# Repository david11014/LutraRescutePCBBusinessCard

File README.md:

# LutraRescutePCBBusinessCard

# Intro

瀕臨絕種團露恰露恰的 PCB 名片，靈感來自以下直播內容
[【魔女之家#2】見習小魔女水獺的新家大冒險🍻【露恰露恰．Vtuber】](https://youtu.be/RvgKsK7jW5E?t=4198)

感謝[春魚工作室](https://t.co/JhnwOmfZGn)與[里歐](https://twitter.com/leo_chen0912/status/1580262135908945920)授權使用圖片

This is a PCB business card of LutraLutra, the idea is inspired by the blow live video [【魔女之家#2】見習小魔女水獺的新家大冒險🍻【露恰露恰．Vtuber】](https://youtu.be/RvgKsK7jW5E?t=4198).

Thanks to [春魚工作室](https://t.co/JhnwOmfZGn) and [里歐](https://twitter.com/leo_chen0912/status/1580262135908945920) for the permission to use image.

# BOM
|Ref                     |Qnty |Value        |Footprint                                                  |Description                                     |Vendor                             |
|------------------------|-----|-------------|-----------------------------------------------------------|------------------------------------------------|-----------------------------------|
|BT1,                    |1    |Battery_Cell |Battery:BatteryHolder_Keystone_1060_1x2032                 |Single-cell battery                             |https://ok.100y.com.tw/Goods/52684 |
|C1,                     |1    |0.1uF        |Capacitor_SMD:C_0805_2012Metric_Pad1.18x1.45mm_HandSolder  |Unpolarized capacitor                           |https://ok.100y.com.tw/Goods/99587 |
|C2, C3, C4, C5,         |4    |10uF         |Capacitor_SMD:C_0805_2012Metric_Pad1.18x1.45mm_HandSolder  |Unpolarized capacitor                           |https://ok.100y.com.tw/Goods/42857 |
|C6,                     |1    |0.001uF      |Capacitor_SMD:C_0805_2012Metric_Pad1.18x1.45mm_HandSolder  |Unpolarized capacitor                           |https://ok.100y.com.tw/Goods/124188|
|D1, D2, D3, D4, D5, D6  |6    |LED          |Img:LED_0805_2012Metric_Pad1.15x1.40mm_HandSolder          |Light emitting diode                            |https://ok.100y.com.tw/Goods/99164 |
|R1, R2,                 |2    |100K         |Resistor_SMD:R_0805_2012Metric_Pad1.20x1.40mm_HandSolder   |Resistor                                        |https://ok.100y.com.tw/Goods/123451|
|R3, R4, R5, R6, R7, R8, |6    |2K           |Resistor_SMD:R_0805_2012Metric_Pad1.20x1.40mm_HandSolder   |Resistor                                        |https://ok.100y.com.tw/Goods/123312|
|SW1,                    |1    |SW_DPDT_x2   |Img:Switch_MSK-01A                                         |Switch, dual pole double throw, separate symbols|https://ok.100y.com.tw/Goods/139685|
|SW2,                    |1    |SW_Push      |Button_Switch_SMD:SW_SPST_TL3342                           |Push button switch, generic, two pins           |https://ok.100y.com.tw/Goods/98045 |
|U1,                     |1    |LMC555CM/NOPB|Package_SO:SOIC-8_3.9x4.9mm_P1.27mm                        |CMOS Timer, 555 compatible, SOIC-8              |https://ok.100y.com.tw/Goods/56713 |

# License

<br />本著作係採用<a rel="license" href="http://creativecommons.org/licenses/by-nc-sa/4.0/">創用 CC 姓名標示-非商業性-相同方式分享 4.0 國際 授權條款</a>授權.

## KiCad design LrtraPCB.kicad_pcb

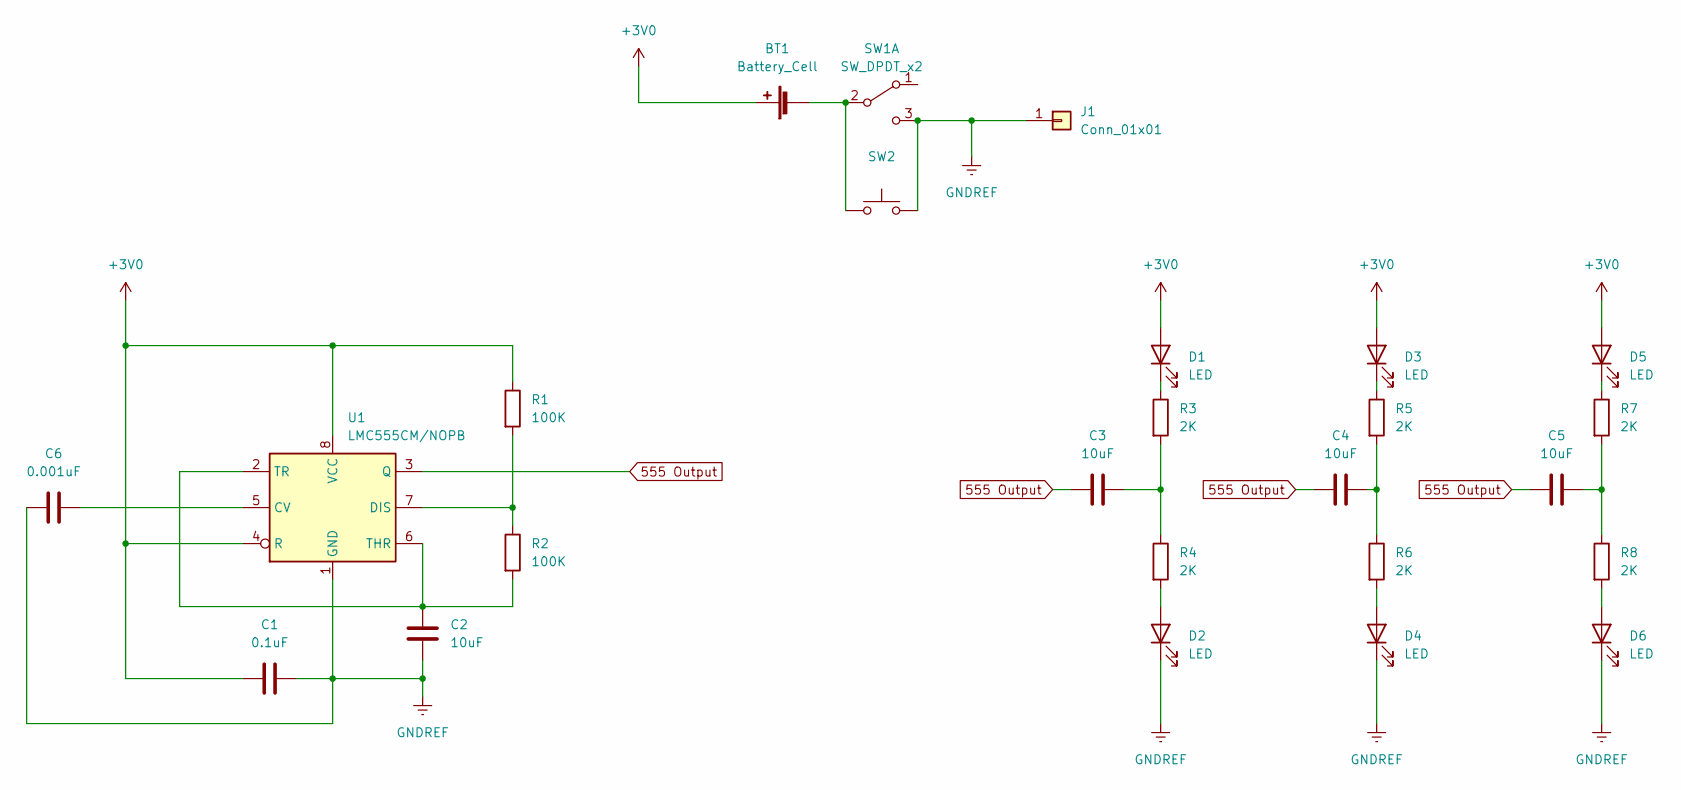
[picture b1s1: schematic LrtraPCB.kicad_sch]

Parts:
BT1: Battery_Cell; BatteryHolder_Keystone_1060_1x2032
C1: 0.1uF; C_0805_2012Metric_Pad1.18x1.45mm_HandSolder
C2, C3, C4, C5: 10uF; C_0805_2012Metric_Pad1.18x1.45mm_HandSolder
C6: 0.001uF; C_0805_2012Metric_Pad1.18x1.45mm_HandSolder
D1, D4, D5: LED; LED_0805_2012Metric_Pad1.15x1.40mm_HandSolder_Flower_small
D2, D3, D6: LED; LED_0805_2012Metric_Pad1.15x1.40mm_HandSolder_Flower
J1: Conn_01x01; Lutra_QRCode
R1, R2: 100K; R_0805_2012Metric_Pad1.20x1.40mm_HandSolder
R3, R4, R5, R6, R7, R8: 2K; R_0805_2012Metric_Pad1.20x1.40mm_HandSolder
SW1: SW_DPDT_x2; Switch_MSK-01A
SW2: SW_Push; SW_SPST_TL3342
U1: LMC555CM/NOPB; SOIC-8_3.9x4.9mm_P1.27mm

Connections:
555 Output: C3.1, C4.1, C5.1, U1.3 (Q)
+3V0: BT1.1 (+), C1.2, D1.2 (A), D3.2 (A), D5.2 (A), R1.1, U1.4 (R), U1.8 (VCC)
GNDREF: C1.1, C2.2, C6.2, D2.1 (K), D4.1 (K), D6.1 (K), J1.1, SW1.3 (C), SW1.4 (A), SW2.2, U1.1 (GND); also elsewhere on the board
unnamed 3: BT1.2 (-), SW1.2 (B), SW2.1; also elsewhere on the board
unnamed: C2.1, R2.2, U1.2 (TR), U1.6 (THR)
unnamed: C3.2, R3.2, R4.1
unnamed: C4.2, R5.2, R6.1
unnamed: C5.2, R7.2, R8.1
unnamed: C6.1, U1.5 (CV)
unnamed: D1.1 (K), R3.1
unnamed: D2.2 (A), R4.2
unnamed: D3.1 (K), R5.1
unnamed: D4.2 (A), R6.2
unnamed: D5.1 (K), R7.1
unnamed: D6.2 (A), R8.2
unnamed: R1.2, R2.1, U1.7 (DIS)

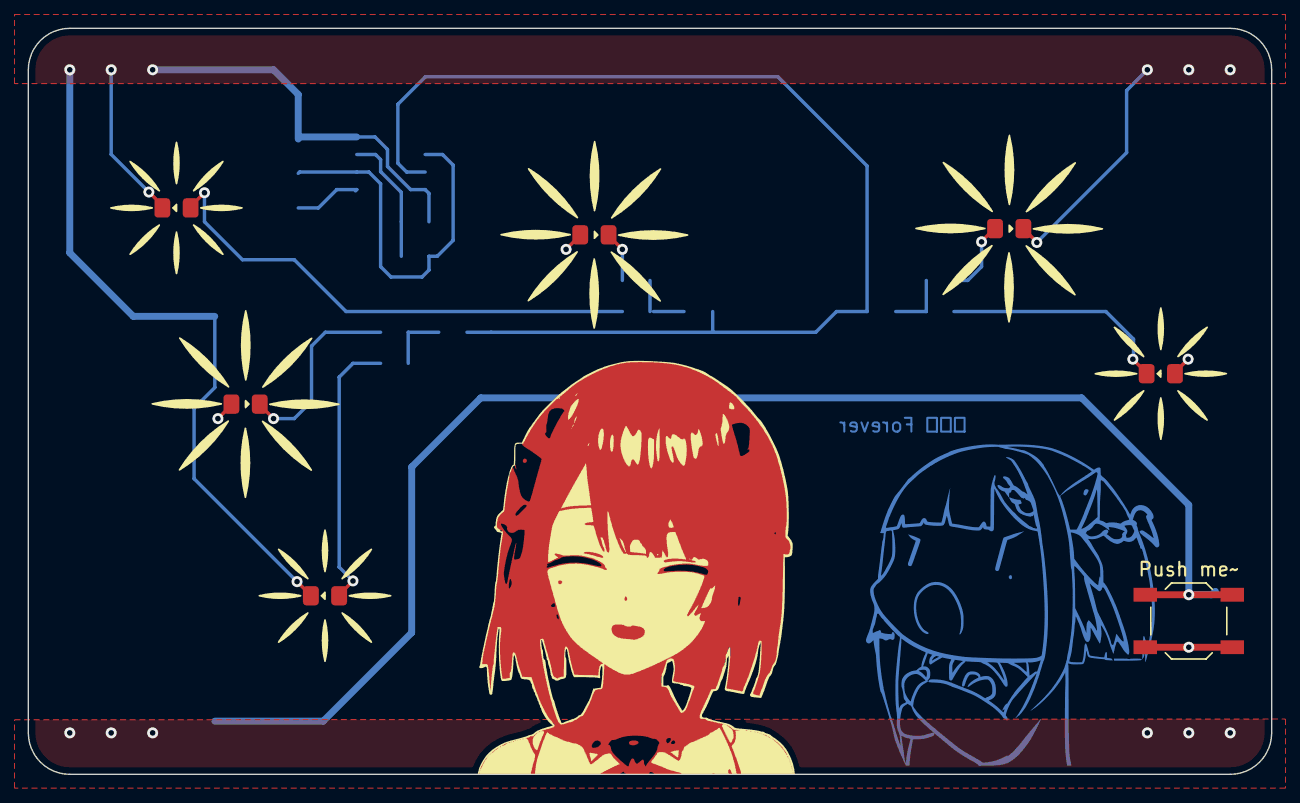
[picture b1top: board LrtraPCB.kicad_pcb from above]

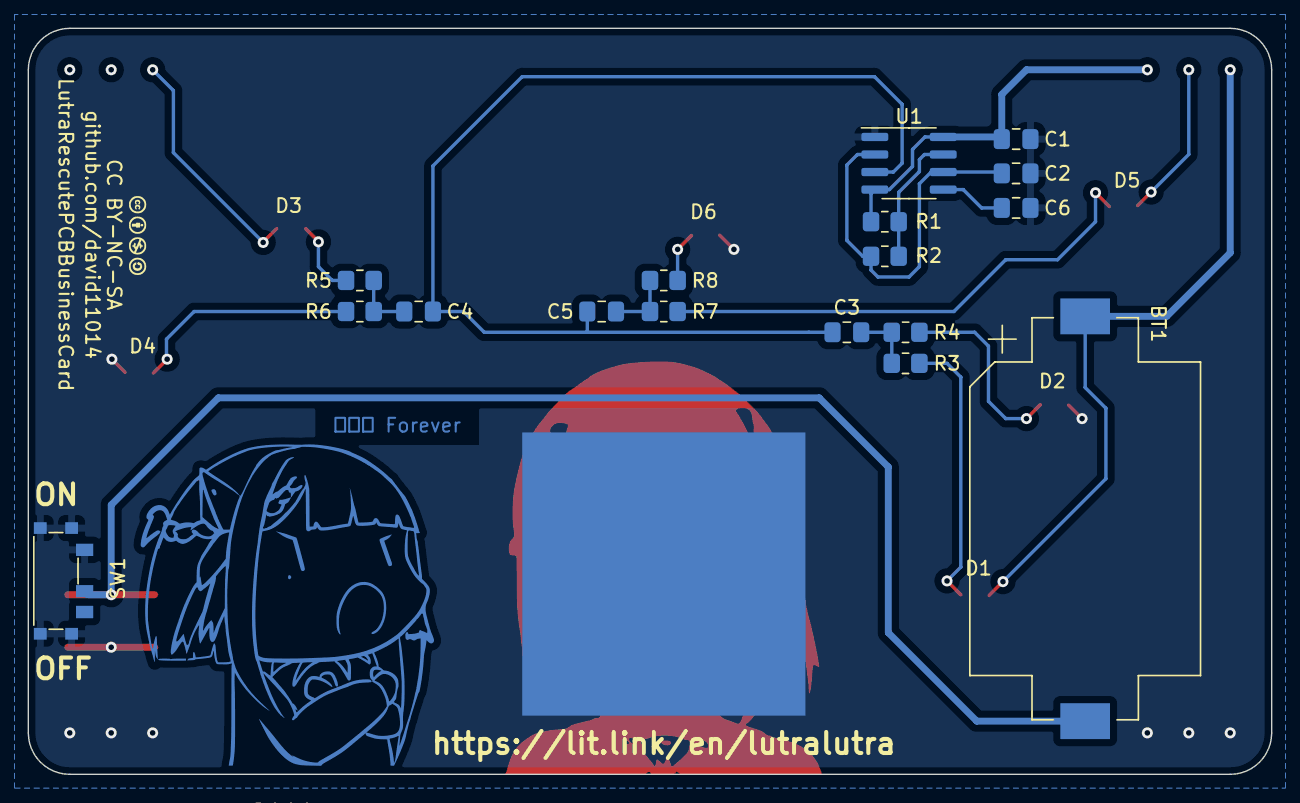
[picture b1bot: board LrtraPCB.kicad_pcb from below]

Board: 2 copper layers, 90.0 x 54.0 mm, 26 parts (19 on the bottom side), 16 nets.

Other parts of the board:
LutraRescutePCBBusinessCard: CC-BY-NC-SA
Push me~: SW_Push; SW_SPST_TL3342
https://lit.link/en/lutralutra: Conn_01x01; Lutra_QRCode

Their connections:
GNDREF: Push me~.2, https://lit.link/en/lutralutra.1; also elsewhere on the board
unnamed 3: Push me~.1; also elsewhere on the board

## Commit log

2022-10-23 [add] Add First version
2022-10-23 [modify] modify sign
2022-10-23 [modify] 更新鋪銅
2022-10-23 [add] Add Gerbers file
2022-10-23 [Add] Add README
2022-10-23 Add Licence
2022-10-23 [modify] modify license in read me
2022-10-23 Add sch image
2022-10-25 [Add] Add BOM Table
2022-11-19 Add menual
2022-11-20 Update manual

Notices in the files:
README.md:
License:
CC BY-NC-SA 4.0
